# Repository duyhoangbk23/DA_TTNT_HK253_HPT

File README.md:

Báo báo đồ án thực tập ngoài trường
Khoa khoa học và kĩ thuật máy tính
Họ và tên: Hoàng Anh Duy 
MSSV:2310458
Thời gian thực tập 15/6-14/8
Đề tài: Phát triển hệ thống IoT hỗ trọ giám sát và quản lí thời gian thực cho hệ thống bảo trì máy lọc nước.

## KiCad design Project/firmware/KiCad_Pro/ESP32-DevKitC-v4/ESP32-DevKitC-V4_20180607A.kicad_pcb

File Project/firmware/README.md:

# Firmware ESP32

## Yêu cầu
- Cài `Visual Studio Code`
- Cài extension `PlatformIO IDE`
- Kết nối board ESP32 qua cáp USB

## Cấu hình hiện tại
- Board: `ESP32-DevKitC-v4 / ESP32-NodeMCU-32S 38Pins`
- MCU  : ` ESP32-WROOM-32`
- Framework: `Arduino`
- Baud monitor: `115200`

## Định danh telemetry

Firmware chính dùng `Config::Device::MCU_ID` và publish trường JSON `mcu_id` dạng
chuỗi. Ví dụ: `"mcu_id": "ESP32_001"`. Simulator `Message_sending_test` cũng dùng
cùng tên `MCU_ID`/`mcu_id`.

## Build code
Mở thư mục `Project/firmware` trong VS Code, sau đó chạy:

```bash
pio run
```

Lệnh này sẽ biên dịch toàn bộ firmware theo cấu hình trong `platformio.ini`.

## Nạp code vào ESP32
Sau khi build xong, nạp firmware bằng:

```bash
pio run --target upload
```

Nếu máy không tự nhận cổng, chỉ định thủ công:

```bash
pio run --target upload --upload-port COMx
```

Thay `COMx` bằng cổng thực tế của ESP32 trên máy bạn.

## Theo dõi serial
Mở terminal để xem log:

```bash
pio device monitor -b 115200
```

## Quy trình nhanh
1. Mở `Project/firmware`
2. Chạy `pio run`
3. Chạy `pio run --target upload`
4. Mở `pio device monitor -b 115200`

## Lưu ý
- Nếu upload lỗi, kiểm tra lại cổng COM và driver USB-to-UART.
- Nếu board không vào chế độ nạp, giữ nút `BOOT` trong lúc upload.

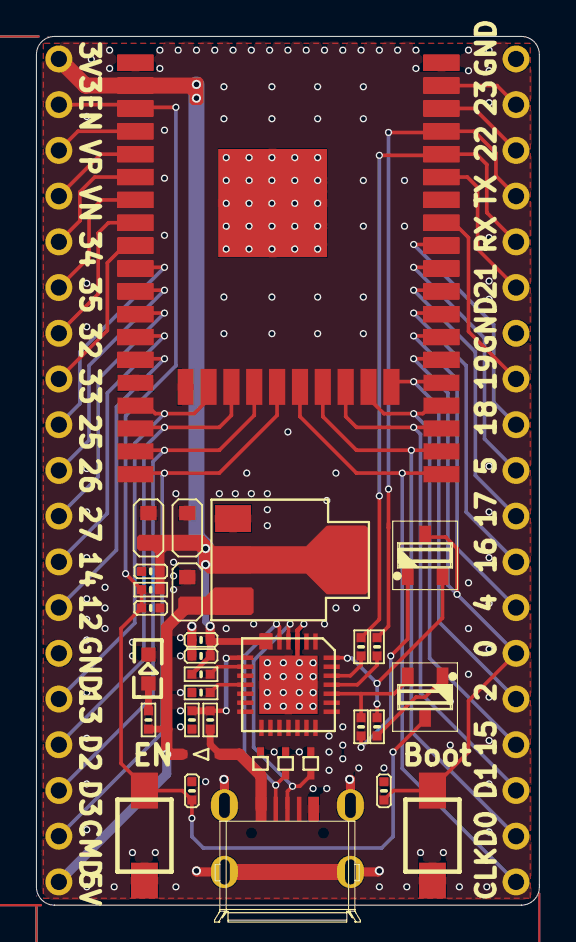
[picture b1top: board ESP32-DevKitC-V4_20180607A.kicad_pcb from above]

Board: 2 copper layers, 27.9 x 48.3 mm, 35 parts (0 on the bottom side), 50 nets.

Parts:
C1, C3, C21: 22uF/10V(20%); C0603
C9, C14, C19, C22: 0.1uF/50V(10%); C0402
C15: 0.1uF/50V(10%)(NC); C0402
C20: 4.7uF/6.3V(10%); C0402
D1: RED LED; 0603D$2F$A
D2: ESP-WROOM-32; ESP32_MODULE
D3: BAT760-7; SOD323
D4, D5, D6: LESD5D5.0CT1G; SOD-523
J1: USB_CON8; USB_5P
J2, J3: CON19X1_2P54; CON19_2P54
Q1, Q2: SS8050-G; SOT-23-3
R2, R24: 2K(5%); R0402
R11, R21, R22: 10K(5%); R0402
R17, R18: 0R(5%); R0402
R23: 10K(5%)(NC); R0402
R25: 22.1K(5%); R0402
R26: 47.5K(5%); R0402
SW1, SW2: SW PUSHBUTTON; SW_3X4X2MM
U1: CP2102N-A01-GQFN28; CP2102_QFN_28P
U2: AMS1117-3.3; SOT-223
U3: ESP32_WROVER(NC); ESP32_MODULE_2COL

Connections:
ACTIVE: R23.2, U1.11
CLK: D2.20, J3.19, U3.20
CMD: D2.19, J2.18, U3.19
D+: D5.1, J1.3, U1.4
D-: D4.1, J1.2, U1.5
DTR: Q2.2, R21.1, U1.28
EN: C9.1, C14.2, D2.3, J2.2, Q1.3, R11.2, SW2.2, U3.3
EXT_5V: C1.2, D3.1, J2.19, R2.1, U2.3
GND: C1.1, C3.1, C9.2, C14.1, C15.1, C19.2, C20.1, C21.1, C22.2, D1.2, D2.1, D2.15, D2.38, D2.39, D4.2, D5.2, D6.2, J1.5, J1.6, J1.7, J1.8, J1.9, J2.14, J3.1, J3.7, R23.1, R26.1, SW1.1, SW2.1, U1.3, U1.29, U2.1, U3.1, U3.15, U3.38, U3.39
IO0: C15.2, D2.25, J3.14, Q2.3, SW1.2, U3.25
IO2: D2.24, J3.15, U3.24
IO4: D2.26, J3.13, U3.26
IO5: D2.29, J3.10, U3.29
IO12: D2.14, J2.13, U3.14
IO13: D2.16, J2.15, U3.16
IO14: D2.13, J2.12, U3.13
IO15: D2.23, J3.16, U3.23
IO16: D2.27, J3.12, U3.27
IO17: D2.28, J3.11, U3.28
IO18: D2.30, J3.9, U3.30
IO19: D2.31, J3.8, U3.31
IO21: D2.33, J3.6, U3.33
IO22: D2.36, J3.3, U3.36
IO23: D2.37, J3.2, U3.37
IO25: D2.10, J2.9, U3.10
IO26: D2.11, J2.10, U3.11
IO27: D2.12, J2.11, U3.12
IO32: D2.8, J2.7, U3.8
IO33: D2.9, J2.8, U3.9
IO34: D2.6, J2.5, U3.6
IO35: D2.7, J2.6, U3.7
NC: D2.32, U3.32
NetD1_1: D1.1, R2.2
NetQ1_1: Q1.1, R21.2
NetQ2_1: Q2.1, R22.2
NetR24_2: R24.2, U1.9
NetR25_1: R25.1, R26.2, U1.8
RTS: Q1.2, R22.1, U1.24
RXD: R17.1, U1.25
RXD0: D2.34, J3.5, R18.2, U3.34
SD0: D2.21, J3.18, U3.21
SD1: D2.22, J3.17, U3.22
SD2: D2.17, J2.16, U3.17
SD3: D2.18, J2.17, U3.18
SENSOR_VN: D2.5, J2.4, U3.5
SENSOR_VP: D2.4, J2.3, U3.4
TXD: R18.1, U1.26
TXD0: D2.35, J3.4, R17.2, U3.35
VBUS: D3.2, D6.1, J1.1, R25.2
VDD33: C3.2, C19.1, C20.2, C21.2, C22.1, D2.2, J2.1, R11.1, R24.1, U1.6, U1.7, U2.2, U2.4, U3.2

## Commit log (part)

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2026-06-23 week1_update
2026-06-23 week1_update2
2026-06-28 update week2
2026-06-30 update frontend "agent implementation src code"
2026-06-30 update frontend
